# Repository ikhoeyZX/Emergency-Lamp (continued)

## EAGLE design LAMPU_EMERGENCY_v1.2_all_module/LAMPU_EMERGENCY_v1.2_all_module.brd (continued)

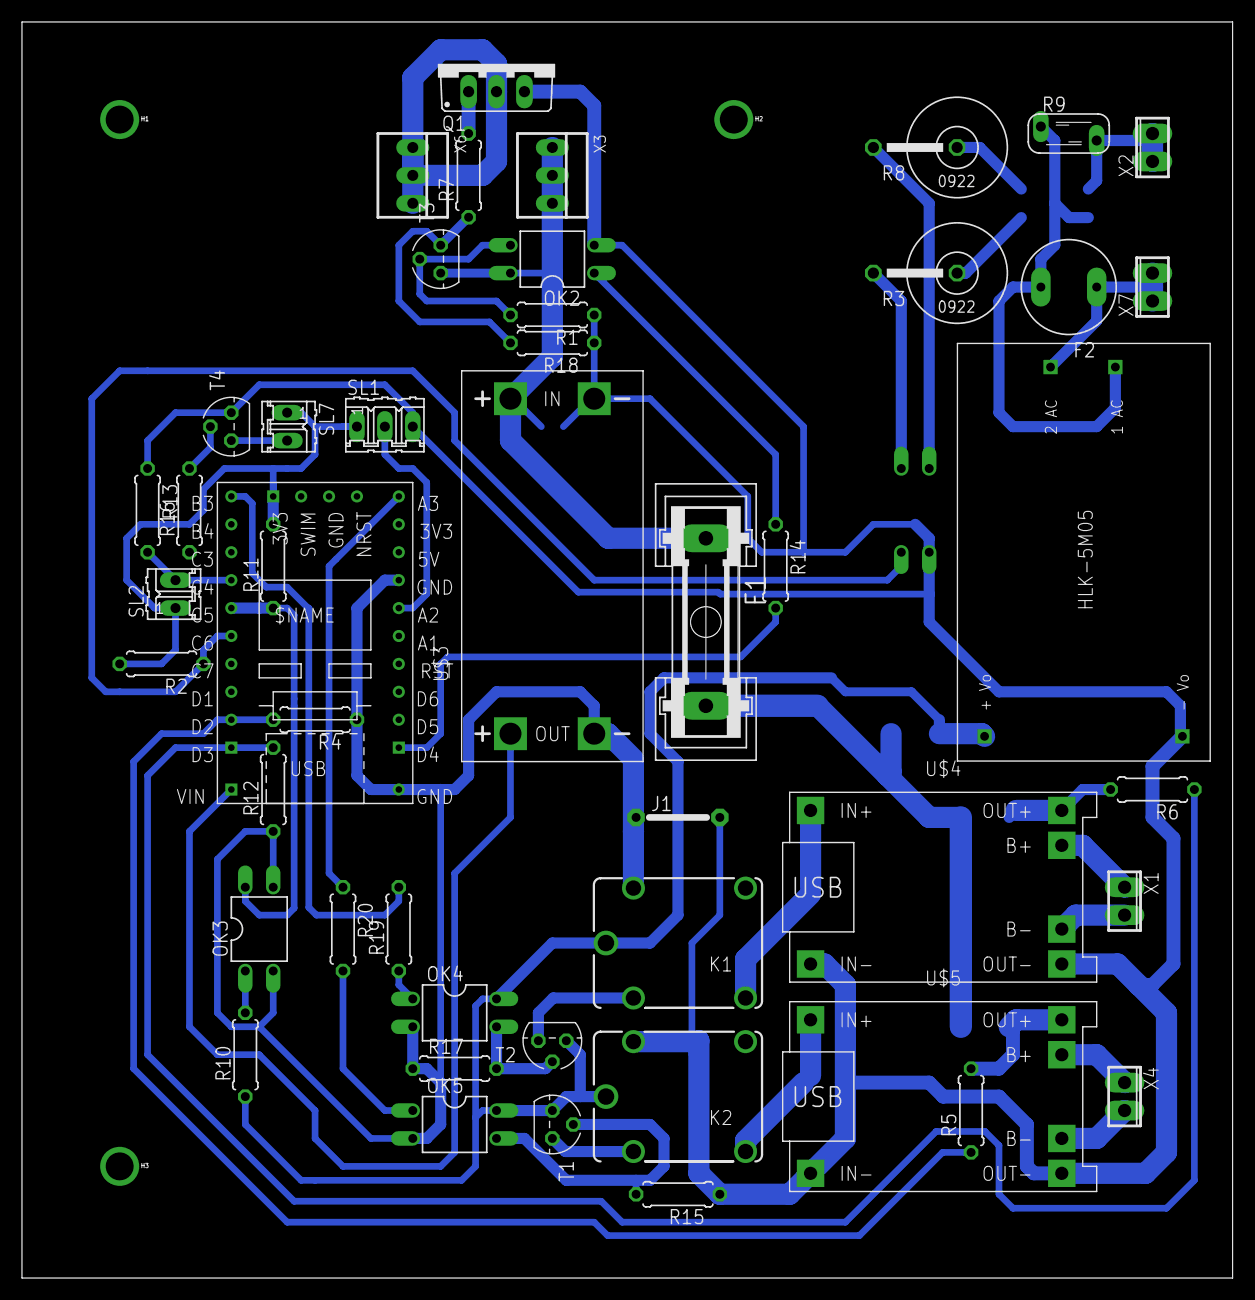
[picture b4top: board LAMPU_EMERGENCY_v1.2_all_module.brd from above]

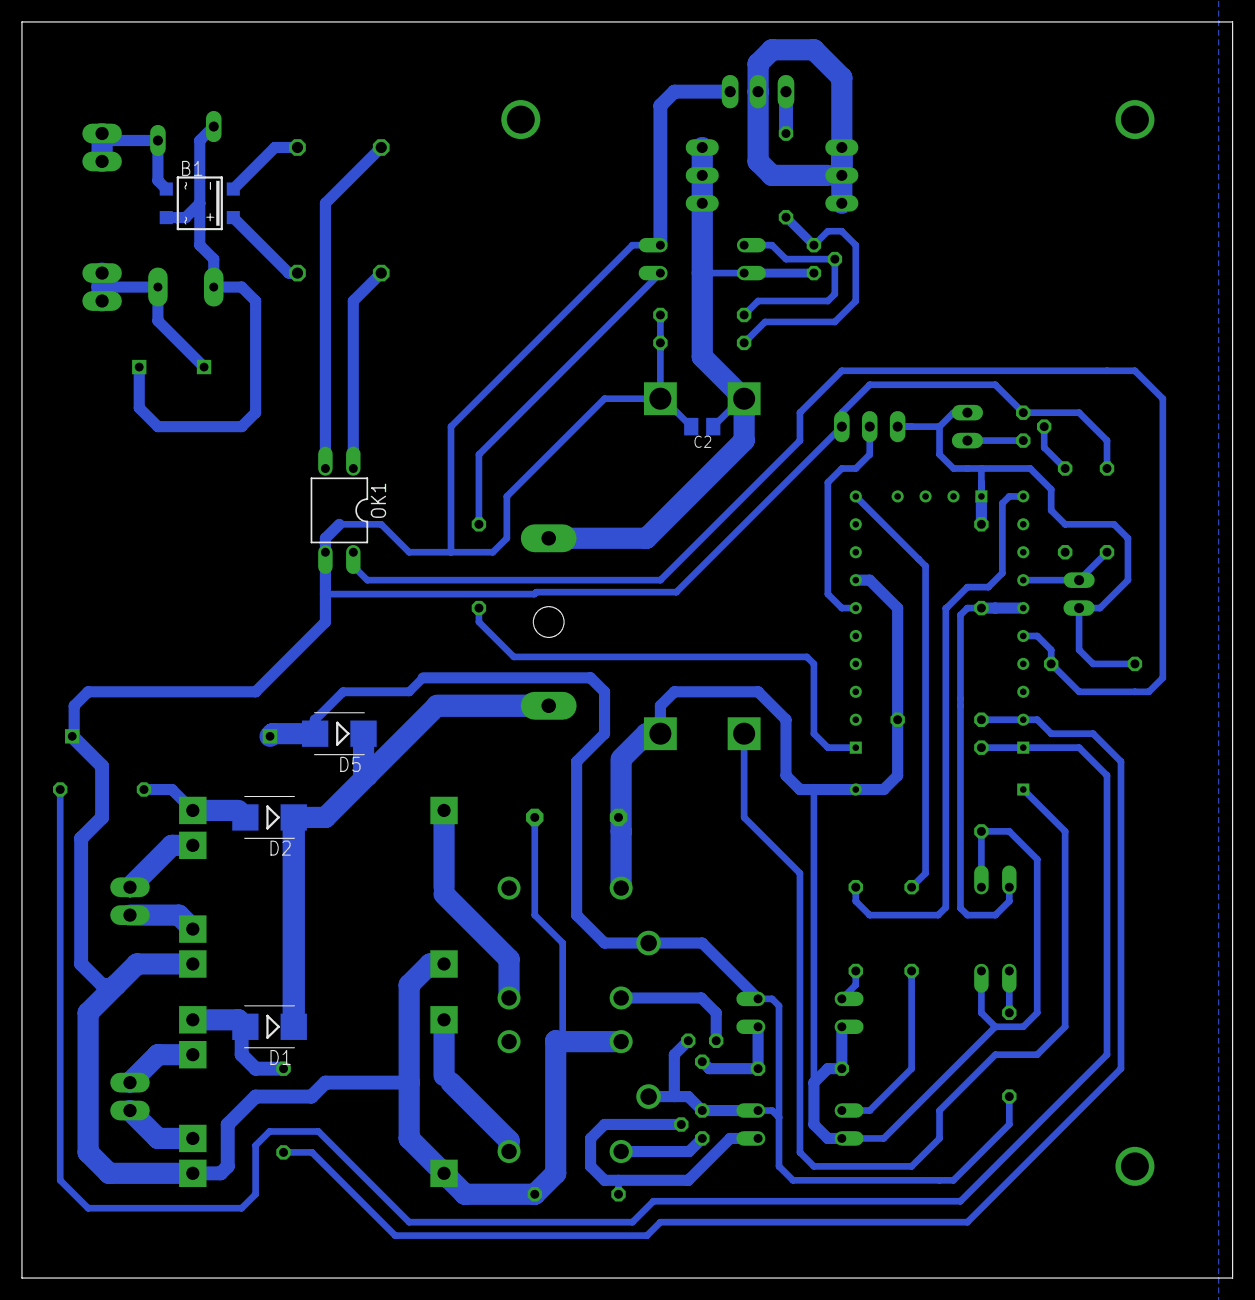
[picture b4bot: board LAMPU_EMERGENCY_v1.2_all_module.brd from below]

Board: 2 copper layers, 110.2 x 114.3 mm, 57 parts (6 on the bottom side), 45 nets.

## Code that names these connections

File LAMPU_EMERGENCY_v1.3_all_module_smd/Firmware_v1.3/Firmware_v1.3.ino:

/*********
//
// Lampu Emergency v1.3 REV 0, (c) 2023 - 2024 Undens Corp.
// DESIGNED FOR STM8 SMD board
//
**********/

#include <Serial.h>
#define digitalPinToInterrupt(p)  ((p)==(p)) // workaround-fix, empty macro is missing in header files

/*********
//
// PIN
//
**********/
// DIGITAL
const uint8_t BAT1_REY=2;   // Battery charger 1 mosfet
const uint8_t BAT2_REY=4;   // Battery charger 2 mosfet
const uint8_t BUZZER=5;     // Speaker buzzer type
const uint8_t V5_ON=7;      // Adapt detector
const uint8_t AC_DET=8;     // AC voltage detector
const uint8_t VIB_SEN_X=PA1;  // Vibrator sensor
const uint8_t VIB_SEN_Y=PA2;  // Vibrator sensor
const uint8_t MOSFETOUT=13; // PIN LED_OUT

// ANALOG
const uint8_t LDR=PC4;
const uint8_t BAT1=PD2;
const uint8_t BAT2=PD3;

// VARIABLE
volatile bool quakedet = LOW;
const uint16_t LDRtrig = 200;	// Set LDR detect as no light
const uint16_t limit = 2560; 	// Set limit count to reread battery since no need read battery every milis, max uint16_t is 65535

uint16_t bat1cal = 512;		 // Battery calibration, need DMM to calibrate it
uint16_t bat2cal = 512;		 // Battery calibration, need DMM to calibrate it

float bat1s=0,bat2s = 0;		// Set default battery condition
float battery_full = 4.18;  // battery full
float battery_low = 3.35;   // battery empty

uint16_t count = 0;         // counting to trigger "limit"
bool buzzcall = false;      // time loop buzzer ring

/*********
//
// Speaker
//
**********/
void buzzer(uint16_t duration){  // max 65535ms should be enough
  digitalWrite(BUZZER,HIGH);
  delay(duration);
  digitalWrite(BUZZER,LOW);
  delay(duration/2);
}
 

/*********
//
// Read battery
//
**********/
float baterai(uint8_t pinbat, uint16_t batcal, uint8_t relaypin, bool pilih){  // read battery
  float a=0; 
  for(uint8_t b=0; b<10; b++){    // Smoothing battery value
    a = a + ((analogRead(pinbat) * (3.3 / batcal)));
    delay(1);
  }
  a = a/10;
  
  if(!pilih){ // flipped since P-channel mosfet
    if(a >= battery_full){ // when battery full
      digitalWrite(relaypin, LOW);  
    }else if(a <= 1){  // when no battery
      digitalWrite(relaypin, LOW); 
    }else if(a <= (battery_full - 0.28) && a > 1){  // when battery low
      digitalWrite(relaypin, HIGH);
    }
  }else{ // when battery finished charger
    digitalWrite(relaypin, LOW);
  }

  return a;   // return battery value
}

void ledbuildin(){
  digitalWrite(LED_BUILTIN, LOW);     // turn the LED off (HIGH is the voltage level)
  delay(10);                          // wait for a second
  digitalWrite(LED_BUILTIN, HIGH);    // turn the LED on by making the voltage LOW
  delay(10);   
}

bool smoothlogic(uint16_t sensorin){  // smoothing digital AC detector
  uint8_t acc=0;

  for(uint8_t c=0; c<5; c++){
    acc = acc + digitalRead(sensorin);
    delay(1);
  }
  if(acc >3){   // when AC voltage detected high for 3x
    return HIGH;
  }

  return LOW;
}

void ISR(){ // Interrupt because quake sensor trigger (tilt sensor)
  quakedet = HIGH;
  digitalWrite(BUZZER,HIGH);
}

/*********
//
// Setup
//
**********/
void setup() {
  // DIGITAL PIN
  pinMode(BAT1_REY, OUTPUT);
  pinMode(BAT2_REY, OUTPUT);
  pinMode(BUZZER, OUTPUT);
  pinMode(V5_ON, INPUT_PULLUP);
  pinMode(AC_DET, INPUT_PULLUP);
  pinMode(VIB_SEN_X, INPUT_PULLUP);
  pinMode(VIB_SEN_Y, INPUT_PULLUP);
  pinMode(MOSFETOUT, OUTPUT);
  pinMode(LED_BUILTIN, OUTPUT);

  // ANALOG INPUT PIN: BAT1, BAT2, LDR
  digitalWrite(BAT1_REY,HIGH);
  digitalWrite(BAT2_REY,HIGH);
  digitalWrite(MOSFETOUT,HIGH);

///////////////////////////////////////////////////
// uncomment Serial_begin bellow to calibrate bat1 and bat2 after that you can disable this again
///////////////////////////////////////////////////

  // Serial_begin(9600); 

///////////////////////////////////////////////////

  ledbuildin();
  attachInterrupt(digitalPinToInterrupt(VIB_SEN_X), ISR, CHANGE);
  attachInterrupt(digitalPinToInterrupt(VIB_SEN_Y), ISR, CHANGE);
  buzzer(10);
  buzzer(20);
  buzzer(10);

  // Read battery now!
  bool v5_on = digitalRead(V5_ON);
  bat1s = baterai(BAT1, bat1cal, BAT1_REY, v5_on);
  bat2s = baterai(BAT2, bat2cal, BAT2_REY, v5_on);
}


/*********
//
// Main
//
**********/
void loop() {
  bool v5_on = smoothlogic(V5_ON);
  bool ac = smoothlogic(AC_DET);
  uint16_t bacaldr = analogRead(LDR);

  if(buzzcall){

  }else if(v5_on == HIGH && ac == LOW && !buzzcall){ // ring buzzer if adaptor not yet on but AC voltage exist
    buzzer(50);
    buzzer(5);
    buzzer(20);
    buzzer(10);

    buzzcall = true;
  }

  if(count > limit){
    bat1s = baterai(BAT1, bat1cal, BAT1_REY, v5_on);  // Read battery 1
    bat2s = baterai(BAT2, bat2cal, BAT2_REY, v5_on);  // Read battery 2
    ledbuildin();  // blink led

///////////////////////////////////////////////////
// uncomment bellow this to calibrate battery1 and battery2
///////////////////////////////////////////////////

    // Serial_print_s("\nBat1: ");
    // Serial_println_f(bat1s);
    // Serial_print_s("Bat2: ");
    // Serial_println_f(bat2s);

///////////////////////////////////////////////////
    
    count = 0; //reset counter
    buzzcall = false;
 }else{
    count++;
 }

///////////////////////////////////////////////////
// uncomment bellow this to debug sensors pin output
///////////////////////////////////////////////////

    // Serial_print_s("D5v: ");
    // Serial_println_i(v5_on);
    // Serial_print_s("DAC: ");
    // Serial_println_i(ac);
    // Serial_print_s("SGMP: ");
    // Serial_println_i(quakedet);
    // Serial_print_s("SLDR: ");
    // Serial_println_u(bacaldr);

///////////////////////////////////////////////////


  if(quakedet == HIGH && bacaldr < LDRtrig ){   // Quake detected and it happen at night
    digitalWrite(MOSFETOUT, HIGH);
    ledbuildin();
//    Serial_println_s("GMP_MLM");
    delay(500);
    quakedet= LOW;
  }else if(quakedet== HIGH){  // Quake detected and it happen at morning or afternoon
    digitalWrite(MOSFETOUT, LOW);
    ledbuildin();
//    Serial_println_s("GMP_SNG");
    quakedet = LOW;
  }
  digitalWrite(BUZZER,LOW); // Turn off buzzer after detect quake


  if(!buzzcall){

  }else if(bat1s <= battery_low && bat2s <= battery_low && ac == HIGH){ // Turn off mosfet output because low battery
    digitalWrite(MOSFETOUT, LOW);
//    Serial_println_s("LWBAT");
    delay(10000);
  }else if(bat1s < (battery_low + 0.2) && bat2s <= (battery_low + 0.2) && ac == HIGH && !buzzcall){ // Turn off mosfet output and ring speaker because low battery
    digitalWrite(MOSFETOUT, HIGH);
//    Serial_println_s("LWBAT_WRN");
    buzzer(110);
    buzzer(80);
    buzzer(110);
    buzzcall = true;
  }else if(ac == HIGH && bacaldr < LDRtrig){  // Turn on mosfet because no AC voltage detected
    digitalWrite(MOSFETOUT, HIGH);
//    Serial_println_s("NOACMLM"); 
  }else if(bat1s < 1 && bat2s < 1){   // Turn off mosfet output and ring speaker because battery not detected
    digitalWrite(MOSFETOUT, LOW);
    buzzer(20);
    buzzer(60);
    buzzer(20);
//    Serial_println_s("NOBAT");
    delay(2000);
  }else{      // Turn off mosfet output since no quake and ac voltage detected
//    Serial_println_s("MOSOFF");
    digitalWrite(MOSFETOUT, LOW);
  }
}

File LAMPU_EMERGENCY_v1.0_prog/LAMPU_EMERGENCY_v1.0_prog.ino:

/*********
//
// Lampu Emergency v1.0, (c) 2023 Undens
//
**********/
#include <ESP8266WiFi.h>


/*********
//
// PIN
//
**********/
const uint8_t BAT1_REY=2;
const uint8_t BAT2_REY=15;
const uint8_t RELAY_PWR=4;
//const uint8_t SHORT_DET=15;
const uint8_t V5_ON=5;
const uint8_t VIB_SEN=14;
const uint8_t PLEX_A=0;
const uint8_t PLEX_B=12;
const uint8_t DIGITAL=13;
const uint8_t MOSFETOUT=3; // PIN LED_OUT
const uint8_t LED_MANUAL=16;
volatile bool adagempa = LOW;
uint8_t cek5v=0;
bool baterai1penuh = LOW; 
bool baterai2penuh = LOW; 

/*********
//
// Vibration sensor
//
**********/
void IRAM_ATTR GEMPA() {
  digitalWrite(MOSFETOUT, HIGH);
  adagempa = HIGH;
}

/*********
//
// Speaker
//
**********/
void Putarbuzzer(uint durasi){
    digitalWrite(PLEX_B, LOW);
    pinMode(DIGITAL, OUTPUT);
    delay(10); 
    digitalWrite(DIGITAL,HIGH);
    delay(durasi);
    digitalWrite(DIGITAL,LOW);
    delay(durasi/2);
    pinMode(DIGITAL, INPUT_PULLUP);
    delay(10);
    digitalWrite(PLEX_B, HIGH);
} 

/*********
//
// Read battery
//
**********/
float baterai(bool plex){
  float a=0;
  float b;
  digitalWrite(PLEX_A, plex);
  delay(10);
  for(b=0;b<3;b++){
    a = a + (analogRead(A0) * (3.3 / 330));
    delay(50);
  }
  a = a/3;
  return a;
}

void bateraistatus(float pinbat, uint8_t relaypin, bool batid, bool psu){
  bool vin;
  
  if(psu == LOW){
    cek5v=0;
    digitalWrite(relaypin, HIGH);
    batid = LOW;
  }else{
    if(pinbat >= 4.1){
      digitalWrite(relaypin, HIGH);
      batid = HIGH;
    }else if(pinbat <= 4.09 &&pinbat >= 3.8 && batid == HIGH){ 
      digitalWrite(relaypin, HIGH);
    }else if(pinbat <= 4.09 &&pinbat >= 3.8 && batid == LOW){
      
      digitalWrite(relaypin, LOW);
    }else if(pinbat <= 3.79 &&pinbat >= 2){
      batid = LOW;
      vin = cekpsu(V5_ON);
      if(vin == LOW && cek5v < 5){
        digitalWrite(relaypin, LOW);
        digitalWrite(RELAY_PWR, LOW);
        cek5v = cek5v+1;
      }else if(vin == HIGH){
        cek5v=0;
      }else{
        Putarbuzzer(5);
        Putarbuzzer(10);
        Putarbuzzer(3);
        digitalWrite(RELAY_PWR, HIGH);
        digitalWrite(relaypin, HIGH);
        delay(1000);
      }
    }else if(pinbat <= 2){
      digitalWrite(relaypin, HIGH);
    }else{

    }
  }
}

/*********
//
// AC VOLTAGE / Adaptor (ON/OFF)
// 
// pindigital=
//    DIGITAL = 220VAC 
//    V5_ON = ADAPTOR
//
**********/
bool cekpsu(uint8_t pindigital){
  bool a;
  digitalWrite(PLEX_B, HIGH);
  pinMode(DIGITAL, INPUT_PULLUP);
  delay(10);
  a = digitalRead(pindigital);
  if(a == LOW){
    return HIGH;
  }else{
    return LOW;
  }
}

/*********
//
// Setup
//
**********/
void setup() {
//  Serial.begin(74880);
  WiFi.mode(WIFI_OFF);

  pinMode(BAT1_REY, OUTPUT);
  pinMode(BAT2_REY, OUTPUT);
  pinMode(RELAY_PWR, OUTPUT);
  pinMode(V5_ON, INPUT_PULLUP);
  pinMode(PLEX_A, OUTPUT);
  pinMode(PLEX_B, OUTPUT);
  pinMode(MOSFETOUT, OUTPUT);
  pinMode(LED_MANUAL, INPUT);
  digitalWrite(PLEX_B,HIGH);
  digitalWrite(BAT1_REY,LOW);
  digitalWrite(BAT2_REY,HIGH); 
  digitalWrite(MOSFETOUT,LOW);
  Putarbuzzer(10);
  Putarbuzzer(20);
  Putarbuzzer(10);
  attachInterrupt(digitalPinToInterrupt(VIB_SEN), GEMPA, FALLING);
  digitalWrite(BAT1_REY,HIGH);
}


/*********
//
// Main
//
**********/
void loop() {
  float a,b;
  bool ac,V5OFF;

  ac = cekpsu(DIGITAL);

  bool tombol = digitalRead(LED_MANUAL);
  if(adagempa == HIGH){
    Putarbuzzer(150);
    Putarbuzzer(10);
    Putarbuzzer(120);
    Putarbuzzer(60);
    adagempa = LOW;
  }else{  }

  a = baterai(HIGH);
  bateraistatus(a, BAT1_REY, baterai1penuh, ac);
  b = baterai(LOW);
  bateraistatus(b, BAT2_REY, baterai2penuh, ac);
  // Serial.print(F("Bat 1: "));
  // Serial.println(a);
  // Serial.print(F("Bat 2: "));
  // Serial.println(b);

  if(a >= 4.19 && b >= 4.19){
    digitalWrite(RELAY_PWR, HIGH);
  }else if(a <15&& b >= 4.19){
   digitalWrite(RELAY_PWR, HIGH);
  }else if(b <1 && a >= 4.19){
    digitalWrite(RELAY_PWR, HIGH);
  }else{ }

  if(a <= 3.41 && b <= 3.41 && ac == LOW){
    digitalWrite(MOSFETOUT, LOW);
    digitalWrite(RELAY_PWR, HIGH);
    delay(6000);
  }else if(a <= 3.42 && b <= 3.42 && ac == LOW){ 
    digitalWrite(MOSFETOUT, LOW);
    digitalWrite(RELAY_PWR, HIGH);
    Putarbuzzer(110);
    Putarbuzzer(80);
    Putarbuzzer(110);
    delay(10000);
  }else{
    if(tombol == LOW){
      digitalWrite(MOSFETOUT, HIGH);
      delay(2000);
    }else{ 
      if(ac == LOW){
        digitalWrite(MOSFETOUT, HIGH);
        digitalWrite(RELAY_PWR, HIGH);
      }else{
        digitalWrite(MOSFETOUT, LOW);
      }
      delay(1500);
    }
  }
}

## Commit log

2024-04-22 Add files
    First contents
2024-04-22 Update LICENSE
2024-04-22 How to build
2024-04-22 add how to build
2024-04-22 add build info
2024-09-07 add smd 2 layers board
2024-09-14 Split X and Y vibration sensors
    separate it, maybe someone use sensors have different type
2024-10-23 change battery limit
